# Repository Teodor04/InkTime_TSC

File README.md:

# InkTime Watch

A low-power e-paper smartwatch built around the **nRF52840**, designed for long battery life, sunlight readability, BLE connectivity, and essential wearable functionality such as notifications, timekeeping, basic motion tracking, and haptic feedback.

The platform integrates a **1.54" e-paper display**, **BLE 5.0**, **USB-C charging**, **battery fuel gauging**, **accelerometer-based activity tracking**, and a **haptic feedback driver**, all inside a compact custom enclosure.

---

## Overview

InkTime Watch is a custom smartwatch hardware platform optimized for:
- **Ultra-low power consumption**
- **Always-readable e-paper display**
- **Bluetooth Low Energy communication**
- **Battery-powered operation**
- **Compact wearable form factor**

The system is centered on the **Nordic nRF52840**, which handles BLE communication, USB connectivity, GPIO control, and communication with all peripherals over SPI and I2C.

---

## Block Diagram

```text
                              ┌─────────────────────────────────────────────┐
                              │                 nRF52840                   │
                              │          MCU + BLE + USB Interface         │
                              │                                             │
                              │ SPI ───────────────► E-Paper Display        │
                              │ I2C ───────────────► BMA421                 │
                              │ I2C ───────────────► MAX17048               │
                              │ I2C ───────────────► BQ25180                │
                              │ I2C ───────────────► DRV2605L               │
                              │ GPIO ──────────────► Buttons                │
                              │ GPIO ──────────────► PFET Display Switch    │
                              │ SWDIO / SWDCLK ────► Tag-Connect SWD        │
                              │ D+ / D- ───────────► USB Type-C             │
                              │ ANT ───────────────► 2.4 GHz Antenna        │
                              │ XC1 / XC2 ─────────► 32 MHz Crystal         │
                              │ XL1 / XL2 ─────────► 32.768 kHz Crystal     │
                              └─────────────────────────────────────────────┘
                                              │
                                              ▼
                              ┌─────────────────────────────────────────────┐
                              │                 Power Tree                 │
                              │ USB 5V → BQ25180 → SYS → RT6160 → 3.3V    │
                              │ LiPo → BQ25180 BAT                         │
                              │ LiPo → MAX17048                            │
                              │ 3.3V → PFET → Switched EPD Rail           │
                              └─────────────────────────────────────────────┘

Bill of Materials (BOM)
Active & Critical Components
+----------------------+-------------------------------------------+-----------+------------+----------------------+
| Component            | Description                               | Package   | Part       | Datasheet            |
+----------------------+-------------------------------------------+-----------+------------+----------------------+
| nRF52840             | BLE 5.0 Cortex-M4F MCU                   | AQFN-73   | C190794    | Nordic nRF52840      |
| BQ25180YBGR          | 1A LiPo Charger (I2C)                    | DSBGA-8   | BQ25180YBGR| TI BQ25180           |
| MAX17048G+T10        | Fuel Gauge                              | TDFN-8    | C2682616   | Maxim MAX17048       |
| RT6160AWSC           | 3.3V Buck-Boost                         | WLCSP-15  | C7065276   | Richtek RT6160A      |
| BMA421               | IMU / Step Counter                      | LGA-12    | C5242966   | Bosch BMA421         |
| DRV2605YZFR          | Haptic Driver                           | DSBGA-9   | C527464    | TI DRV2605           |
| 2450AT18B100E        | 2.4GHz Antenna                          | 1206      | C2917717   | Johanson             |
| USBLC6-2SC6Y         | USB ESD Protection                      | SOT-23-6  | C2969755   | ST USBLC6-2          |
| KH-TYPE-C-16P        | USB-C Connector                         | SMD       | C168704    | Generic              |
| 503480-2400          | 24-pin FPC (EPD)                        | SMD       | —          | Molex                |
| DMG2305UX            | P-MOSFET (EPD power)                    | SOT-23    | C2940629   | Diodes Inc           |
| MBR0530              | Schottky Diode                          | SOD-123   | C77336     | Onsemi               |
| TC2030-IDC           | SWD Tag-Connect                         | PCB       | —          | Tag-Connect          |
+----------------------+-------------------------------------------+-----------+------------+----------------------+

Passive Components
+-----------------------------+-----------+--------+-----+-----------------------------+
| Component                   | Value     | Package| Qty | Function                    |
+-----------------------------+-----------+--------+-----+-----------------------------+
| Decoupling capacitors       | 100nF     | 0201   | 5   | MCU + peripherals           |
| Crystal load capacitors     | 12pF      | 0201   | 4   | Crystals                    |
| Bulk capacitors             | 4.7uF     | 0402   | 4   | Power buffering             |
| USB capacitor               | 4.7uF     | 0402   | 1   | USB stability               |
| Power capacitors            | 22uF      | 0402   | 2   | RT6160 input               |
| Charger capacitors          | 1uF       | 0402   | 3   | BQ25180 support            |
| E-paper capacitors          | 1uF / 50V | 0402   | 9   | Display driver             |
| MCU DC/DC inductor          | 10uH      | 0402   | 1   | nRF52840 regulator         |
| Buck-boost inductor         | 0.47uH    | 2012   | 1   | RT6160                     |
| I2C pull-up resistors       | 10k       | 0201   | 2   | SDA / SCL                  |
| USB-C CC resistors          | 5.1k      | 0201   | 2   | USB configuration          |
| Crystal                     | 32 MHz    | 2016   | 1   | MCU / RF clock             |
| Crystal                     | 32.768 kHz| 3215   | 1   | RTC                        |
+-----------------------------+-----------+--------+-----+-----------------------------+

## Hardware Description

### MCU - nRF52840

The **nRF52840** is the central processing unit of the InkTime watch. It integrates:

- **ARM Cortex-M4F** running at **64 MHz**, with floating-point unit
- **Bluetooth Low Energy 5.0**, used for time synchronization, notifications, and wireless communication
- **USB 2.0 Full Speed**, used for charging detection and firmware-related USB functionality
- **1 MB Flash** and **256 KB RAM**

The MCU coordinates all peripherals on the board. Communication with external devices is handled through:

- **SPI** for the e-paper display
- **I2C** for the motion sensor, fuel gauge, charger, regulator, and haptic driver

In addition to the communication buses, the MCU also manages:
- GPIO-based control lines for the display
- interrupt lines from peripherals
- button inputs
- haptic enable control
- SWD programming and debugging

---

### Power Architecture

The power system is designed around a rechargeable **single-cell Li-Po battery** and a **USB-C charging interface**.

```text
USB-C --> BQ25180 (charger / power path) --> Battery charging
                                     --> System rail

Battery --> MAX17048 --> battery monitoring
System rail / regulated rail --> MCU + peripherals
Display high-voltage rails --> generated by dedicated E-paper drive circuitry

BQ25180YBGR

The BQ25180 is the main charger and power-path management IC. It:

charges the Li-Po battery
monitors VBUS
provides system power management
generates interrupt/status events through PMIC_INT
communicates with the MCU over I2C
RT6160AWSC

The RT6160AWSC is used in the board power architecture as a switching regulator that helps generate the required regulated rail for the system.

MAX17048G+T10

The MAX17048 is a battery fuel gauge that monitors the battery voltage and estimates the state of charge (SOC) over I2C, allowing the firmware to display battery level and low-battery warnings.

E-Paper Display

The e-paper display is connected through an FPC connector and communicates with the MCU over SPI, together with several control GPIOs.

Signal	Direction	Description
SCK	MCU → EPD	SPI clock
MOSI	MCU → EPD	SPI data
EPD_CS	MCU → EPD	Chip select
EPD_DC	MCU → EPD	Data / Command select
EPD_RST	MCU → EPD	Hardware reset
EPD_BUSY	EPD → MCU	Busy flag

The display power rail is switched through a dedicated P-channel MOSFET, controlled by the MCU, so the panel can be powered only when needed. This reduces idle leakage and improves battery life.

The display driver circuitry generates the dedicated voltages required by the e-paper panel, such as:

PREVGH
PREVGL
VCOM
other gate/source driving rails required by the display
Motion Sensor - BMA421

The BMA421 is a low-power 3-axis accelerometer connected over I2C. It provides:

motion detection
step counting
orientation and activity-related sensing
interrupt-based wake-up functionality

Two interrupt lines are connected to the MCU:

IMU_INT1 for primary motion/step events
IMU_INT2 for additional event signaling or future extensions

This allows the MCU to remain in a low-power state and wake only when meaningful motion events occur.

Haptic Feedback - DRV2605 + ERM Motor

The DRV2605YZFR haptic driver controls the vibration motor used for user feedback. It connects to the MCU over I2C and also uses a dedicated digital enable signal:

HAPTIC_EN enables or disables the driver
OUT+ / OUT- drive the ERM motor
the chip supports waveform-based playback using its internal effects library

The haptic subsystem is used for:

notifications
alerts
button feedback
warning indications
USB Interface - KH-TYPE-C-16P + USBLC6-2SC6Y

The board uses a USB Type-C connector for charging and USB connectivity.

Main USB-related functions:

battery charging through VBUS
USB 2.0 D+ / D- lines connected to the nRF52840
ESD protection on USB data lines using USBLC6-2SC6Y
USB attach / power detection using the VBUS signal

The USB D+ / D- lines connect directly to the nRF52840 USB transceiver, while the USB-C configuration network ensures proper device operation.

RF Section - 2450AT18B100E Antenna

The board uses a 2.4 GHz chip antenna for BLE communication.

Key layout requirements for the RF section:

the antenna is placed at the PCB edge
copper is removed from the antenna keepout area
no signal traces are routed underneath the antenna
an impedance matching network is placed between the MCU RF pin and the antenna

This section is critical for BLE performance and must follow the recommended RF layout constraints.

SWD Debug - TC2030-IDC

Programming and debugging are performed through a Tag-Connect TC2030-IDC footprint.

The debug interface includes:

SWDIO
SWDCLK
nRESET
3.3V reference
GND

Additional exposed test pads are available for easier bring-up and debugging:

TP_SWDIO
TP_SWDCLK
TP_RESET
TP_3.3V
TP_GND

This allows programming and debugging without a permanently mounted header.

nRF52840 Pinout Specification
Shared I2C Bus

All I2C peripherals share the same bus, with pull-up resistors to 3.3V.

Pin	Function	Connected Devices
P0.06	SDA	BMA421, MAX17048, BQ25180, RT6160, DRV2605
P0.07	SCL	BMA421, MAX17048, BQ25180, RT6160, DRV2605
SPI Bus - E-Paper Display
Pin	Function	Description
P0.02	SCK	SPI clock for e-paper display
P0.03	MOSI	SPI data to e-paper display
P0.05	CS	E-paper chip select
P0.15	DC	Data / Command select
P0.16	RST	Display hardware reset
P0.17	BUSY	Display busy/status input
Display Power Control
Pin	Function	Description
P1.01	PFET Gate Control	Enables/disables the display power rail
Interrupts and Peripheral Control
Pin	Function	Description
P0.08	IMU_INT1	Primary motion / step wake interrupt
P1.08	IMU_INT2	Secondary motion interrupt
P0.10	ALRT	Fuel gauge alert / low battery interrupt
P0.11	PMIC_INT	Charger interrupt / status signal
P0.12	HAPTIC_EN	Enables the haptic driver
Physical Buttons

All buttons are connected as active-low inputs to GND.

Pin	Function
P0.13	Up Button
P0.14	Down Button
P1.00	Enter / Esc Button
Clocks and Debug
Pin / Signal	Function
XC1 / XC2	32 MHz crystal
XL1 / XL2	32.768 kHz crystal
SWDIO	SWD debug data
SWDCLK	SWD debug clock
nRESET	MCU reset
VBUS	USB power / attach detection
D+ / D-	Native USB 2.0
ANT	RF output to matching network and antenna
Pin Assignment Rationale

The pin assignment was chosen to keep routing compact and logically grouped:

I2C on P0.06 / P0.07 allows all low-speed peripherals to share a common bus.
SPI on P0.02 / P0.03 / P0.05 keeps display routing compact toward the FPC connector.
Display control pins are grouped close to the SPI bus to simplify routing.
Interrupt lines are placed on dedicated GPIOs so the MCU can identify wake sources immediately.
Buttons are assigned to GPIOs that can be routed toward the lower PCB edge, where the user interface is located.
HAPTIC_EN is placed near the I2C-related section for compact routing.
PFET gate control is placed on a dedicated GPIO to isolate display power switching from the communication buses.
SWDIO / SWDCLK / RESET are broken out to the Tag-Connect footprint for reliable programming and debug access.
Design Notes
The RF section must be kept clear of copper and routed carefully to preserve BLE performance.
The e-paper display requires dedicated high-voltage driving rails generated by the display power circuitry.
The charger, regulator, and battery monitoring ICs form the core of the power subsystem.
The design uses both communication buses and dedicated GPIO control to balance flexibility, low power, and routing simplicity.

License

This project is intended for educational use unless otherwise specified.

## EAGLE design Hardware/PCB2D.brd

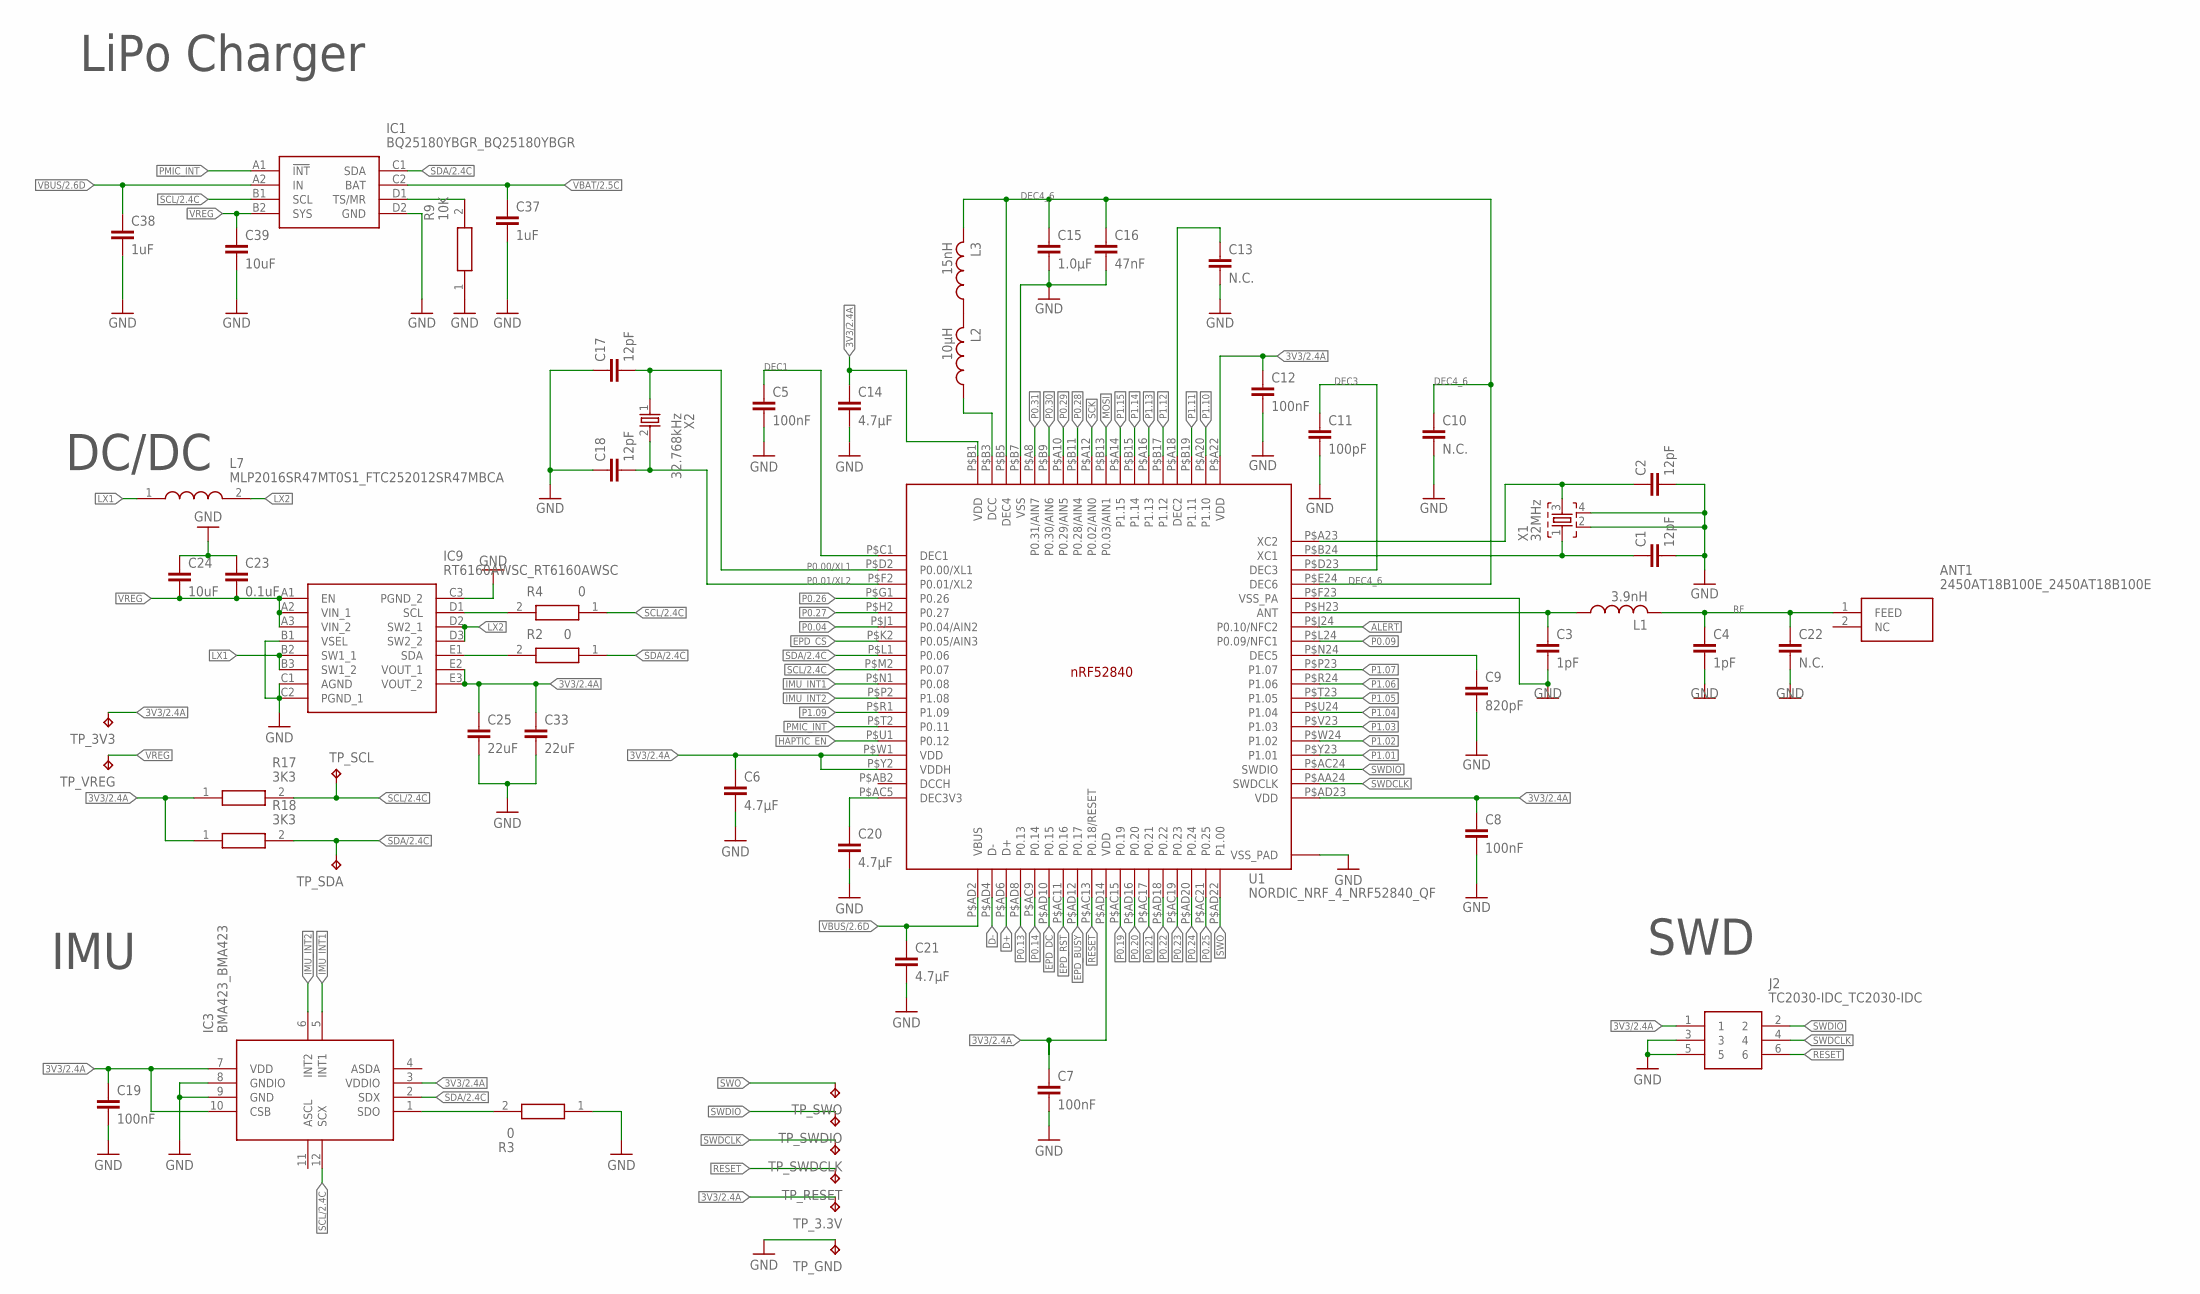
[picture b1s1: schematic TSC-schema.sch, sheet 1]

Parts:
ANT1: 2450AT18B100E_2450AT18B100E; 2450AT18B100E_ANTC3216X140N
C1, C2, C17, C18: 12pF; NORDIC_NRF_3_RESC0201_L
C3, C4: 1pF; NORDIC_NRF_3_RESC0201_L
C5, C7, C8, C12, C19: 100nF; NORDIC_NRF_3_RESC0201_L
C6, C14, C20, C21: 4.7µF; NORDIC_NRF_3_RESC0201_L
C9: 820pF; NORDIC_NRF_3_RESC0201_L
C10, C13, C22: N.C.; NORDIC_NRF_3_RESC0201_L
C11: 100pF; NORDIC_NRF_3_RESC0201_L
C15: 1.0µF; NORDIC_NRF_3_RESC0201_L
C16: 47nF; NORDIC_NRF_3_RESC0201_L
C23: 0.1uF; NORDIC_NRF_3_RESC0201_L
C24, C39: 10uF; NORDIC_NRF_3_RESC0201_L
C25, C33: 22uF; NORDIC_NRF_3_RESC0201_L
C37, C38: 1uF; NORDIC_NRF_3_RESC0402_L
IC1: BQ25180YBGR_BQ25180YBGR; BQ25180YBGR_BGA8C40P2X4_100X155X50
IC3: BMA423_BMA423
IC9: RT6160AWSC_RT6160AWSC; RT6160AWSC_BGA15C40P3X5_140X230X60
J2: TC2030-IDC_TC2030-IDC; TC2030-IDC_TC2030IDC
L1: 3.9nH; NORDIC_NRF_2_RESC0402_L
L2: 10µH; NORDIC_NRF_2_RESC0402_L
L3: 15nH; NORDIC_NRF_2_RESC0402_L
L7: MLP2016SR47MT0S1_FTC252012SR47MBCA; MLP2016SR47MT0S1_INDC2016X100N
R2, R3, R4: 0; CPF0201D7K68C1_0201
R9: 10K; CPF0201D7K68C1_0201
R17, R18: 3K3; CPF0201D7K68C1_0201
TP_3.3V, TP_3V3: HECTOR_WATCH_1_TPTP20R; HECTOR_WATCH_1_TP20R
TP_GND: HECTOR_WATCH_1_TPTP20R; HECTOR_WATCH_1_TP20R
TP_RESET: HECTOR_WATCH_1_TPTP20R; HECTOR_WATCH_1_TP20R
TP_SCL: HECTOR_WATCH_1_TPTP20R; HECTOR_WATCH_1_TP20R
TP_SDA: HECTOR_WATCH_1_TPTP20R; HECTOR_WATCH_1_TP20R
TP_SWDCLK: HECTOR_WATCH_1_TPTP20R; HECTOR_WATCH_1_TP20R
TP_SWDIO: HECTOR_WATCH_1_TPTP20R; HECTOR_WATCH_1_TP20R
TP_SWO: HECTOR_WATCH_1_TPTP20R; HECTOR_WATCH_1_TP20R
TP_VREG: HECTOR_WATCH_1_TPTP20R; HECTOR_WATCH_1_TP20R
U1: NORDIC_NRF_4_NRF52840_QF; NORDIC_NRF_4_AQFN50P700X700X85_HS-74N
X1: 32MHz; NORDIC_NRF_BT-XTAL_2016_N
X2: 32.768kHz; NORDIC_NRF_1_XTAL_3215_N

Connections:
3V3/2.4A: C6.1, C7.1, C8.1, C12.1, C14.1, C19.1, C25.1, C33.1, IC3.3 (VDDIO), IC3.7 (VDD), IC3.10 (CSB), IC9.E2 (VOUT_1), IC9.E3 (VOUT_2), J2.1, R17.1, R18.1, TP_3.3V.TP, TP_3V3.TP, U1.P$A22 (VDD), U1.P$AD14 (VDD), U1.P$AD23 (VDD), U1.P$B1 (VDD), U1.P$W1 (VDD), U1.P$Y2 (VDDH)
ALERT: U1.P$J24 (P0.10/NFC2); also elsewhere on the board
D+: U1.P$AD6 (D+); also elsewhere on the board
D-: U1.P$AD4 (D-); also elsewhere on the board
DEC1: C5.1, U1.P$C1 (DEC1)
DEC3: C11.1, U1.P$D23 (DEC3)
DEC4_6: C10.1, C15.1, C16.1, L3.2, U1.P$B5 (DEC4), U1.P$E24 (DEC6)
EPD_BUSY: U1.P$AD12 (P0.17); also elsewhere on the board
EPD_CS: U1.P$K2 (P0.05/AIN3); also elsewhere on the board
EPD_DC: U1.P$AD10 (P0.15); also elsewhere on the board
EPD_RST: U1.P$AC11 (P0.16); also elsewhere on the board
GND: C1.2, C2.2, C3.2, C4.2, C5.2, C6.2, C7.2, C8.2, C9.2, C10.2, C11.2, C12.2, C13.2, C14.2, C15.2, C16.2, C17.1, C18.1, C19.2, C20.2, C21.2, C22.2, C23.1, C24.1, C25.2, C33.2, C37.2, C38.2, C39.2, IC1.D2 (GND), IC3.8 (GNDIO), IC3.9 (GND), IC9.B1 (VSEL), IC9.C1 (AGND), IC9.C2 (PGND_1), IC9.C3 (PGND_2), J2.3, J2.5, R3.1, R9.1, TP_GND.TP, U1.P$74 (VSS_PAD), U1.P$75 (VSS_PAD), U1.P$76 (VSS_PAD), U1.P$77 (VSS_PAD), U1.P$78 (VSS_PAD), U1.P$79 (VSS_PAD), U1.P$80 (VSS_PAD), U1.P$81 (VSS_PAD), U1.P$82 (VSS_PAD), U1.P$83 (VSS_PAD), U1.P$84 (VSS_PAD), U1.P$85 (VSS_PAD), U1.P$86 (VSS_PAD), U1.P$87 (VSS_PAD), U1.P$88 (VSS_PAD), U1.P$89 (VSS_PAD), U1.P$90 (VSS_PAD), U1.P$B7 (VSS), U1.P$F23 (VSS_PA), X1.2, X1.4; also elsewhere on the board
HAPTIC_EN: U1.P$U1 (P0.12); also elsewhere on the board
IMU_INT1: IC3.5 (INT1), U1.P$N1 (P0.08)
IMU_INT2: IC3.6 (INT2), U1.P$P2 (P1.08)
LX1: IC9.B2 (SW1_1), IC9.B3 (SW1_2), L7.1
LX2: IC9.D2 (SW2_1), IC9.D3 (SW2_2), L7.2
MOSI: U1.P$B13 (P0.03/AIN1); also elsewhere on the board
unnamed: C20.1, U1.P$AC5 (DEC3V3)
unnamed: L2.1, U1.P$B3 (DCC)
unnamed: L2.2, L3.1
unnamed: C1.1, U1.P$B24 (XC1), X1.1
unnamed: C2.1, U1.P$A23 (XC2), X1.3
unnamed: C9.1, U1.P$N24 (DEC5)
unnamed: C13.1, U1.P$A18 (DEC2)
unnamed: C3.1, L1.1, U1.P$H23 (ANT)
unnamed: IC1.D1 (TS/MR), R9.2
unnamed: IC3.1 (SDO), R3.2
unnamed: IC9.D1 (SCL), R4.2
unnamed: IC9.E1 (SDA), R2.2
P0.00/XL1: C17.2, U1.P$D2 (P0.00/XL1), X2.1
P0.01/XL2: C18.2, U1.P$F2 (P0.01/XL2), X2.2
P0.04: U1.P$J1 (P0.04/AIN2)
P0.09: U1.P$L24 (P0.09/NFC1)
P0.13: U1.P$AD8 (P0.13); also elsewhere on the board
P0.14: U1.P$AC9 (P0.14); also elsewhere on the board
P0.19: U1.P$AC15 (P0.19)
P0.20: U1.P$AD16 (P0.20)
P0.21: U1.P$AC17 (P0.21)
P0.22: U1.P$AD18 (P0.22)
P0.23: U1.P$AC19 (P0.23)
P0.24: U1.P$AD20 (P0.24)
P0.25: U1.P$AC21 (P0.25)
P0.26: U1.P$G1 (P0.26)
P0.27: U1.P$H2 (P0.27)
P0.28: U1.P$B11 (P0.28/AIN4)
P0.29: U1.P$A10 (P0.29/AIN5)
P0.30: U1.P$B9 (P0.30/AIN6)
P0.31: U1.P$A8 (P0.31/AIN7)
P1.01: U1.P$Y23 (P1.01); also elsewhere on the board
P1.02: U1.P$W24 (P1.02); also elsewhere on the board
P1.03: U1.P$V23 (P1.03)
P1.04: U1.P$U24 (P1.04)
P1.05: U1.P$T23 (P1.05)
P1.06: U1.P$R24 (P1.06)
P1.07: U1.P$P23 (P1.07)
P1.09: U1.P$R1 (P1.09)
P1.10: U1.P$A20 (P1.10)
P1.11: U1.P$B19 (P1.11)
P1.12: U1.P$B17 (P1.12)
P1.13: U1.P$A16 (P1.13)
P1.14: U1.P$B15 (P1.14)
P1.15: U1.P$A14 (P1.15)
PMIC_INT: IC1.A1 (!INT), U1.P$T2 (P0.11)
RESET: J2.6, TP_RESET.TP, U1.P$AC13 (P0.18/RESET)
RF: ANT1.1 (FEED), C4.1, C22.1, L1.2
SCK: U1.P$A12 (P0.02/AIN0); also elsewhere on the board
SCL/2.4C: IC1.B1 (SCL), IC3.12 (SCX), R4.1, R17.2, TP_SCL.TP, U1.P$M2 (P0.07)
SDA/2.4C: IC1.C1 (SDA), IC3.2 (SDX), R2.1, R18.2, TP_SDA.TP, U1.P$L1 (P0.06)
SWDCLK: J2.4, TP_SWDCLK.TP, U1.P$AA24 (SWDCLK)
SWDIO: J2.2, TP_SWDIO.TP, U1.P$AC24 (SWDIO)
SWO: TP_SWO.TP, U1.P$AD22 (P1.00)
VBAT/2.5C: C37.1, IC1.C2 (BAT)
VBUS/2.6D: C21.1, C38.1, IC1.A2 (IN), U1.P$AD2 (VBUS)
VREG: C23.2, C24.2, C39.1, IC1.B2 (SYS), IC9.A1 (EN), IC9.A2 (VIN_1), IC9.A3 (VIN_2), TP_VREG.TP

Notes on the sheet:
LiPo Charger
DC/DC
IMU
SWD

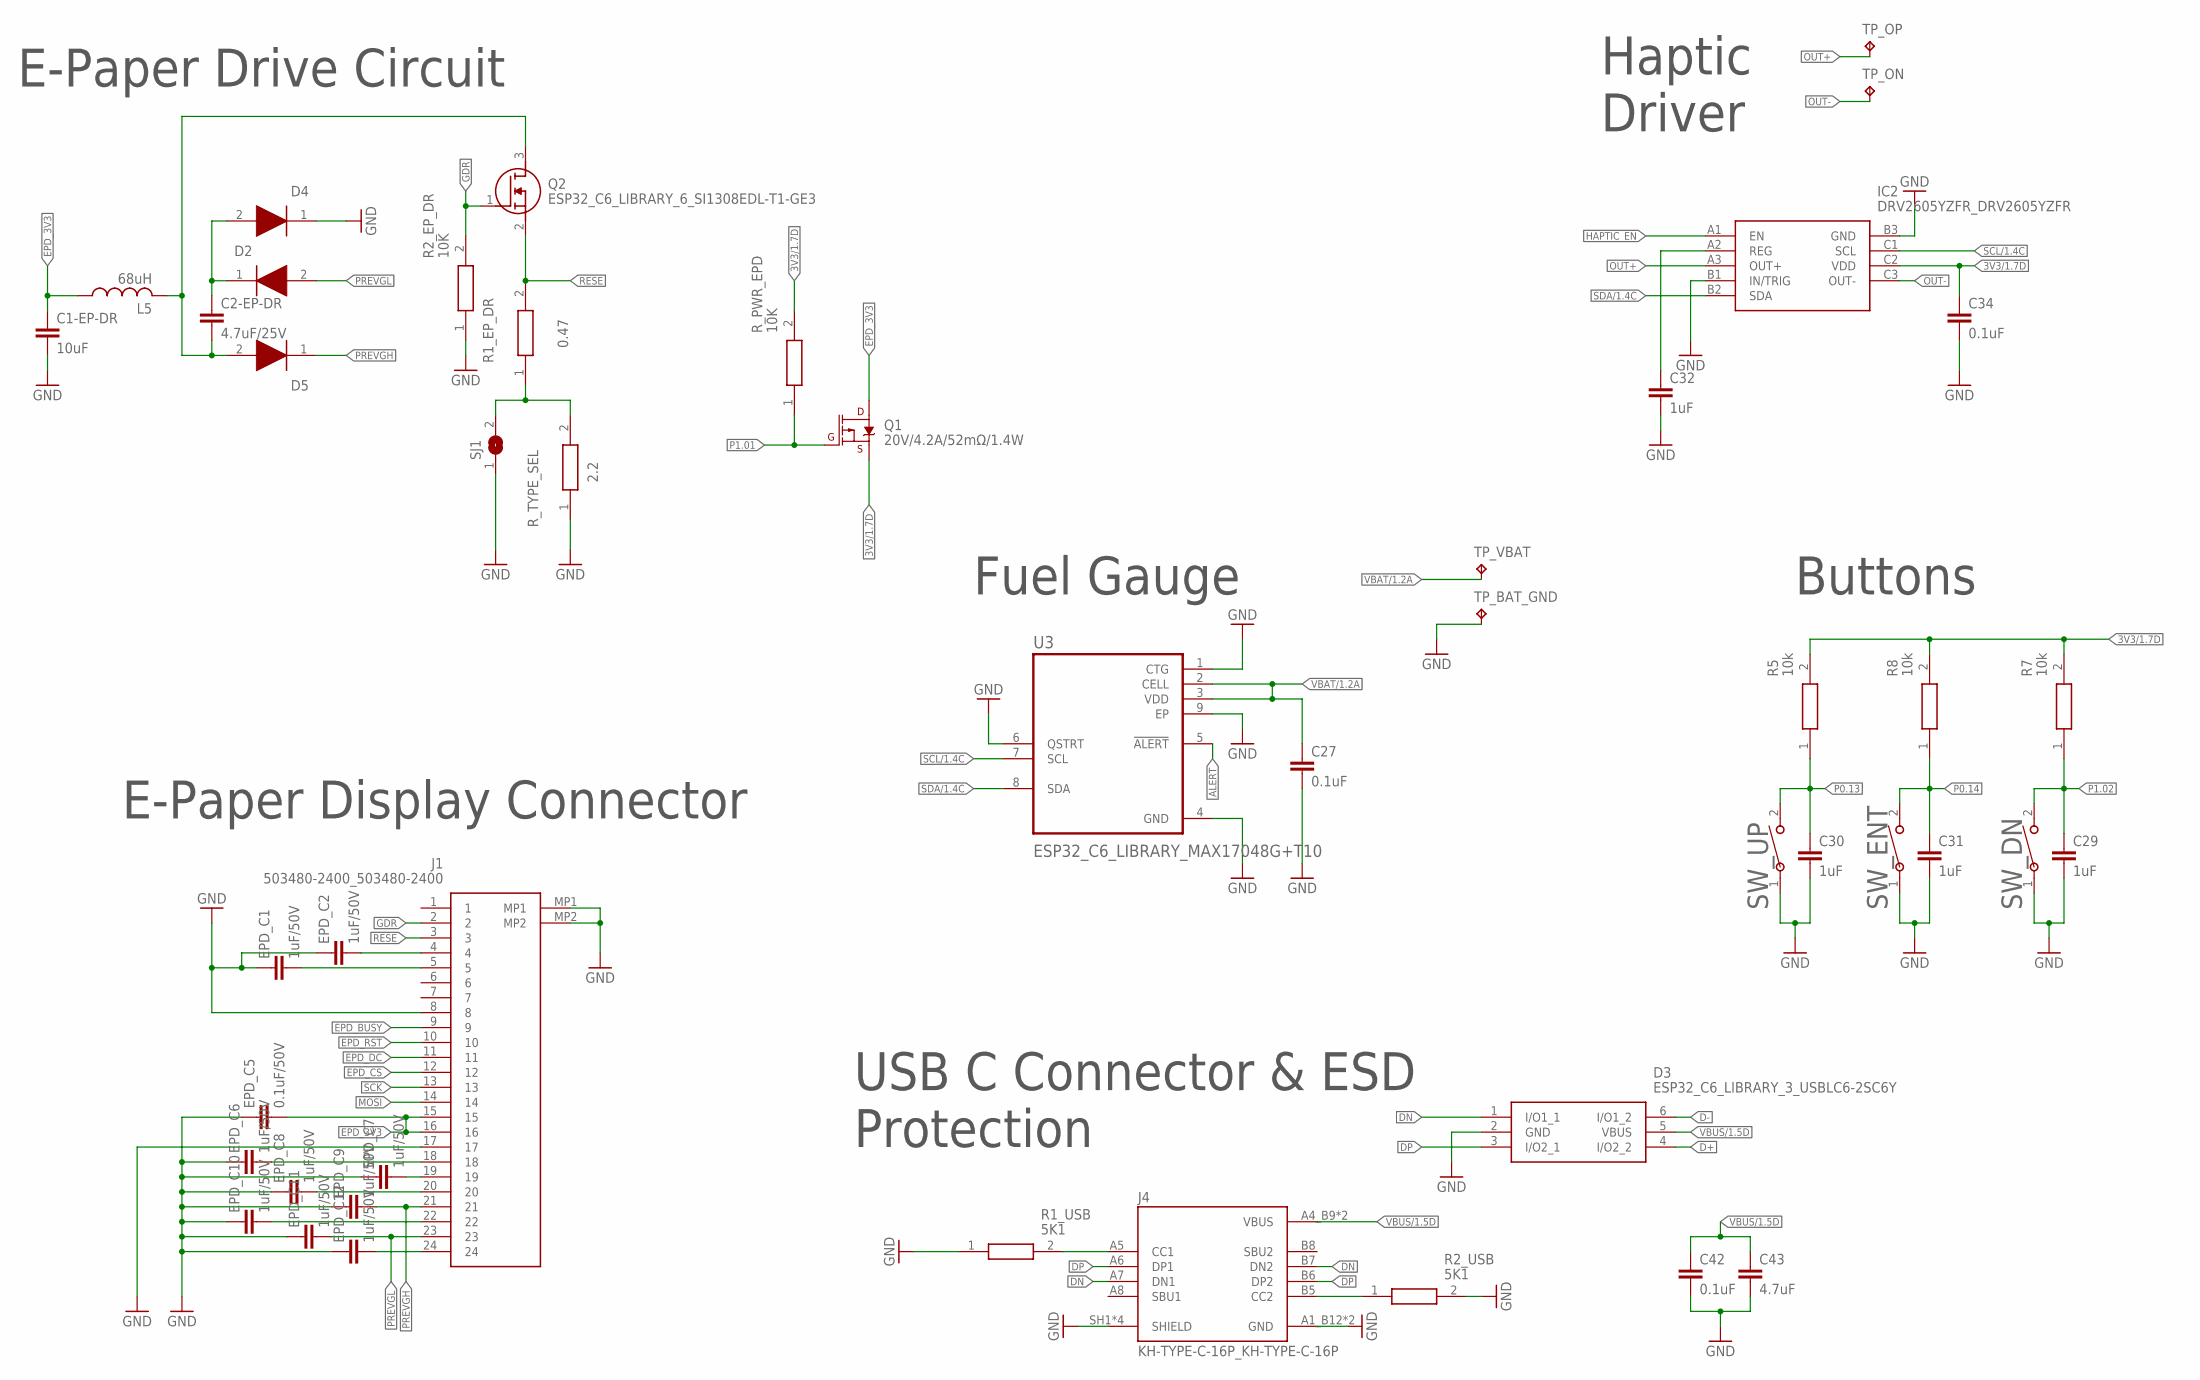
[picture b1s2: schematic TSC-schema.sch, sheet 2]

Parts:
C1-EP-DR: 10uF; NORDIC_NRF_3_RESC0402_L
C2-EP-DR: 4.7uF/25V; NORDIC_NRF_3_RESC0201_L
C27, C34, C42: 0.1uF; NORDIC_NRF_3_RESC0201_L
C29, C30, C31, C32: 1uF; NORDIC_NRF_3_RESC0402_L
C43: 4.7uF; NORDIC_NRF_3_RESC0201_L
D2, D4, D5: ESP32_C6_LIBRARY_5_MBR0530; ESP32_C6_LIBRARY_5_SOD3716X135N
D3: ESP32_C6_LIBRARY_3_USBLC6-2SC6Y; ESP32_C6_LIBRARY_3_SOT95P280X145-6N
EPD_C1, EPD_C2, EPD_C6, EPD_C7, EPD_C8, EPD_C9, EPD_C10, EPD_C11, EPD_C12: 1uF/50V; NORDIC_NRF_3_RESC0201_L
EPD_C5: 0.1uF/50V; NORDIC_NRF_3_RESC0201_L
IC2: DRV2605YZFR_DRV2605YZFR; DRV2605YZFR_BGA9C50P3X3_144X144X62
J1: 503480-2400_503480-2400; 503480-2400_5034802400
J4: KH-TYPE-C-16P_KH-TYPE-C-16P; KH-TYPE-C-16P_KINGHELM_KH-TYPE-C-16P
L5: 68uH; NORDIC_NRF_2_RESC0402_L
Q1: 20V/4.2A/52mΩ/1.4W; ESP32_C6_LIBRARY_4_ESP32_C6_LIBRARY_4_ESP32_C6_LIBRARY_4_ES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
Q2: ESP32_C6_LIBRARY_6_SI1308EDL-T1-GE3; ESP32_C6_LIBRARY_6_SOT65P210X110-3N
R1_EP_DR: 0.47; CPF0201D7K68C1_0201
R1_USB, R2_USB: 5K1; CPF0201D7K68C1_0201
R2_EP_DR: 10K; CPF0201D7K68C1_0201
R5, R7, R8: 10k; CPF0201D7K68C1_0201
R_PWR_EPD: 10K; CPF0201D7K68C1_0201
R_TYPE_SEL: 2.2; CPF0201D7K68C1_0201
SJ1: ESP32_C6_LIBRARY_7_JUMPER_SJ
SW_DN: 2025-10-22_07-23-44_LIBRARY_EVP-AKE31ASW_EVP-AKE3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; 2025-10-22_07-23-44_LIBRARY_SW_EVP-AKE31A_PAN
SW_ENT: 2025-10-22_07-23-44_LIBRARY_EVP-AKE31ASW_EVP-AKE3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; 2025-10-22_07-23-44_LIBRARY_SW_EVP-AKE31A_PAN
SW_UP: 2025-10-22_07-23-44_LIBRARY_EVP-AKE31ASW_EVP-AKE3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; 2025-10-22_07-23-44_LIBRARY_SW_EVP-AKE31A_PAN
TP_BAT_GND: HECTOR_WATCH_1_TPTP20R; HECTOR_WATCH_1_TP20R
TP_ON: HECTOR_WATCH_1_TPTP20R; HECTOR_WATCH_1_TP20R
TP_OP: HECTOR_WATCH_1_TPTP20R; HECTOR_WATCH_1_TP20R
TP_VBAT: HECTOR_WATCH_1_TPTP20R; HECTOR_WATCH_1_TP20R
U3: ESP32_C6_LIBRARY_MAX17048G+T10; ESP32_C6_LIBRARY_SON50P200X200X80-9N

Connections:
3V3/1.7D: C34.1, IC2.C2 (VDD), Q1.2 (S), R5.2, R7.2, R8.2, R_PWR_EPD.2
ALERT: U3.5 (!ALERT); also elsewhere on the board
D+: D3.4 (I/O2_2); also elsewhere on the board
D-: D3.6 (I/O1_2); also elsewhere on the board
DN: D3.1 (I/O1_1), J4.A7 (DN1), J4.B7 (DN2)
DP: D3.3 (I/O2_1), J4.A6 (DP1), J4.B6 (DP2)
EPD_3V3: C1-EP-DR.1, EPD_C5.2, J1.15, J1.16, L5.1, Q1.3 (D)
EPD_BUSY: J1.9; also elsewhere on the board
EPD_CS: J1.12; also elsewhere on the board
EPD_DC: J1.11; also elsewhere on the board
EPD_RST: J1.10; also elsewhere on the board
GDR: J1.2, Q2.1 (G), R2_EP_DR.2
GND: C1-EP-DR.2, C27.2, C29.2, C30.2, C31.2, C32.2, C34.2, C42.2, C43.2, D3.2 (GND), D4.1 (K), EPD_C1.1, EPD_C2.1, EPD_C5.1, EPD_C6.1, EPD_C7.1, EPD_C8.1, EPD_C9.1, EPD_C10.1, EPD_C11.1, EPD_C12.1, IC2.B1 (IN/TRIG), IC2.B3 (GND), J1.8, J1.17, J1.MP1, J1.MP2, J4.A1_B12 (GND), J4.A12_B1 (GND), J4.SH1 (SHIELD), J4.SH2 (SHIELD), J4.SH3 (SHIELD), J4.SH4 (SHIELD), R1_USB.1, R2_EP_DR.1, R2_USB.2, R_TYPE_SEL.1, SJ1.1, SW_DN.1, SW_ENT.1, SW_UP.1, TP_BAT_GND.TP, U3.1 (CTG), U3.4 (GND), U3.6 (QSTRT), U3.9 (EP); also elsewhere on the board
HAPTIC_EN: IC2.A1 (EN); also elsewhere on the board
MOSI: J1.14; also elsewhere on the board
unnamed: C2-EP-DR.2, D5.2 (A), L5.2, Q2.3 (D)
unnamed: C32.1, IC2.A2 (REG)
unnamed: C2-EP-DR.1, D2.1 (K), D4.2 (A)
unnamed: R1_EP_DR.1, R_TYPE_SEL.2, SJ1.2
unnamed: EPD_C2.2, J1.4
unnamed: EPD_C1.2, J1.5
unnamed: J4.A5 (CC1), R1_USB.2
unnamed: EPD_C6.2, J1.18
unnamed: EPD_C7.2, J1.19
unnamed: EPD_C8.2, J1.20
unnamed: EPD_C10.2, J1.22
unnamed: EPD_C12.2, J1.24
unnamed: J4.B5 (CC2), R2_USB.1
OUT+: IC2.A3 (OUT+), TP_OP.TP
OUT-: IC2.C3 (OUT-), TP_ON.TP
P0.13: C30.1, R5.1, SW_UP.2; also elsewhere on the board
P0.14: C31.1, R8.1, SW_ENT.2; also elsewhere on the board
P1.01: Q1.1 (G), R_PWR_EPD.1; also elsewhere on the board
P1.02: C29.1, R7.1, SW_DN.2; also elsewhere on the board
PREVGH: D5.1 (K), EPD_C9.2, J1.21
PREVGL: D2.2 (A), EPD_C11.2, J1.23
RESE: J1.3, Q2.2 (S), R1_EP_DR.2
SCK: J1.13; also elsewhere on the board
SCL/1.4C: IC2.C1 (SCL), U3.7 (SCL)
SDA/1.4C: IC2.B2 (SDA), U3.8 (SDA)
VBAT/1.2A: C27.1, TP_VBAT.TP, U3.2 (CELL), U3.3 (VDD)
VBUS/1.5D: C42.1, C43.1, D3.5 (VBUS), J4.A4_B9 (VBUS), J4.A9_B4 (VBUS)

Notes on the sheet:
E-Paper Drive Circuit
E-Paper Display Connector
Fuel Gauge
Buttons
Haptic Driver
USB C Connector & ESD Protection

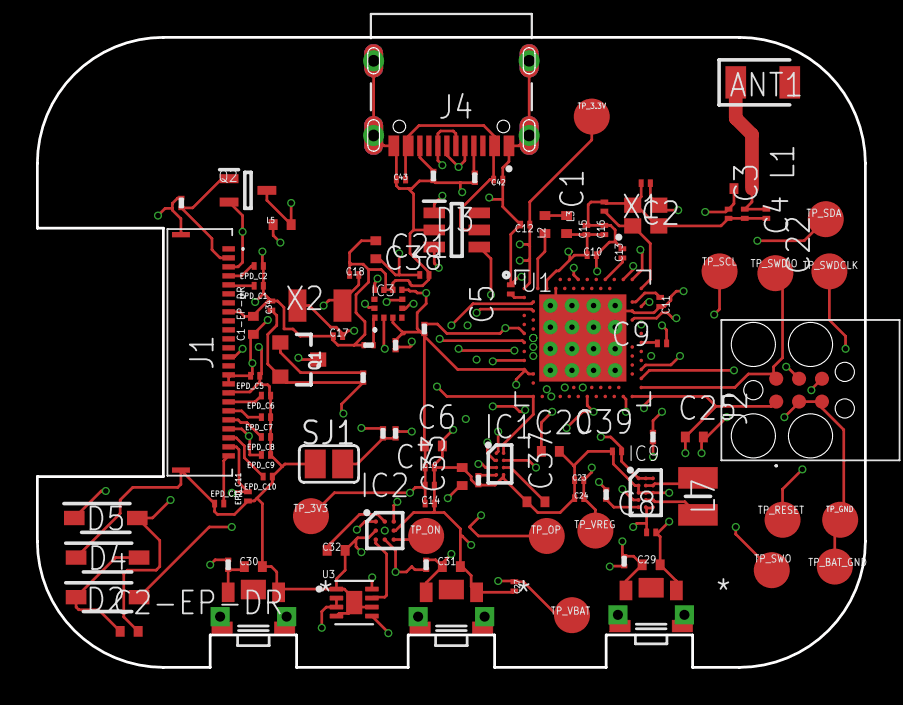
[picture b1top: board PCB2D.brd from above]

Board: 4 copper layers, 46.0 x 35.0 mm, 105 parts (0 on the bottom side), 75 nets.

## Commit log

2026-04-21 Revise README for InkTime Watch project
    Updated project description and added detailed specifications for the InkTime Watch, including hardware architecture, features, and design considerations.
2026-04-21 Add Bill of Materials section to README
    Added Bill of Materials (BOM) section detailing active, critical, and passive components used in the smartwatch project.
2026-04-21 Refactor BOM section for better readability
    Updated the Bill of Materials (BOM) section to improve formatting and clarity.
2026-04-21 Update passive components section in README
2026-04-21 Remove hardware features and architecture details
    Removed detailed hardware features and architecture sections from the README.

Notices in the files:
parts and their libraries:
COPYRIGHT: Copyright (C) 2025 Ultra Librarian. All rights reserved.
